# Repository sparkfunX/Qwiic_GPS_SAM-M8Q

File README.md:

SparkFun Ublox GPS Breakout - SAM-M8Q
===========================================================

[*SparkFun Ublox GPS Breakout - SAM-M8Q (SPX-15106)*](https://www.sparkfun.com/products/15106)

The SAM-M8Q is a small GNSS receiver from Ublox with an impressive number of configurations and the ability to communicate over I2C. 

Repository Contents
-------------------

* **/Documents** - Ublox datasheets and various whitepapers around RTK
* **/Hardware** - Eagle files

Documentation
--------------

* **[Installing an Arduino Library Guide](https://learn.sparkfun.com/tutorials/installing-an-arduino-library)** - Basic information on how to install an Arduino library.
* **[Arduino Library](https://github.com/sparkfun/SparkFun_Ublox_Arduino_Library)** - Arduino Library for the SparkFun Ublox GPS-RTK.

License Information
-------------------

This product is _**open source**_! 

Various bits of the code have different licenses applied. Anything SparkFun wrote is beerware; if you see me (or any other SparkFun employee) at the local, and you've found our code helpful, please buy us a round!

Please use, reuse, and modify these files as you see fit. Please maintain attribution to SparkFun Electronics and release anything derivative under the same license.

Distributed as-is; no warranty is given.

- Your friends at SparkFun.

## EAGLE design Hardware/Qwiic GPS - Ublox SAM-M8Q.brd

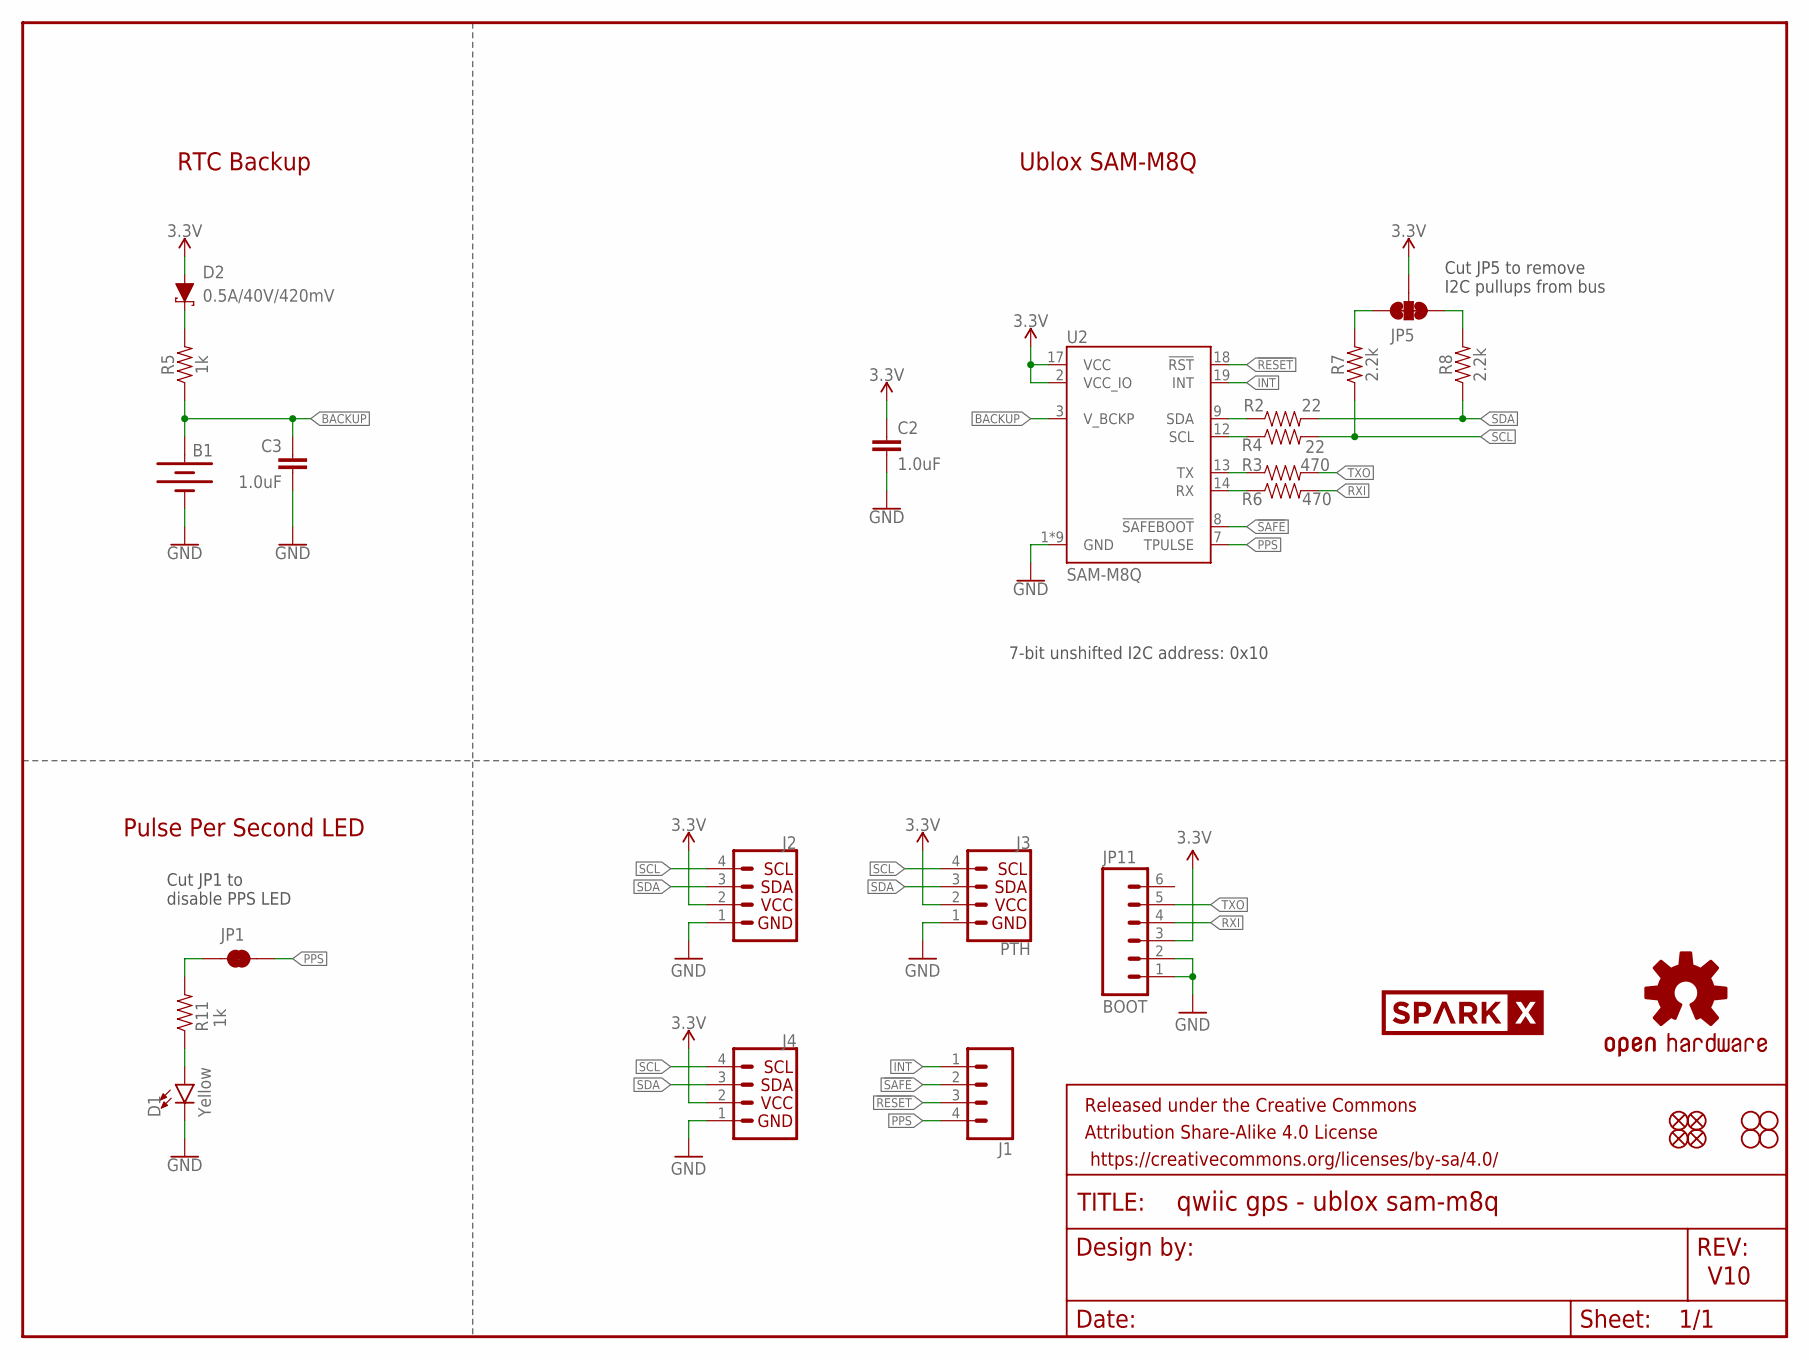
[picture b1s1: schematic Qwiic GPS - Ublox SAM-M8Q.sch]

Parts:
B1: 6.8MM_COIN_CELL; ML414H_IV01E
C2, C3: 1.0uF; 0603
D1: Yellow; LED-0603
D2: 0.5A/40V/420mV; SOD-323
FRAME1: FRAME-LETTER; CREATIVE_COMMONS
J1: CONN_041X04_NO_SILK; 1X04_NO_SILK
J2, J4: I2C_STANDARDQWIIC; 1X04_1MM_RA
J3: PTH; 1X04_NO_SILK
JP1: JUMPER-SMT_2_NC_TRACE_SILK; SMT-JUMPER_2_NC_TRACE_SILK
JP2, JP6, JP7, JP8: FIDUCIALUFIDUCIAL; MICRO-FIDUCIAL
JP3, JP4, JP9, JP10: STAND-OFF
JP5: JUMPER-SMT_3_2-NC_TRACE_SILK; SMT-JUMPER_3_2-NC_TRACE_SILK
JP11: BOOT; 1X06_NO_SILK
LOGO1: OSHW-LOGOMINI; OSHW-LOGO-MINI
R2, R4: 22; 0603
R3, R6: 470; 0603
R5, R11: 1k; 0603
R7, R8: 2.2k; 0603
U2: SAM-M8Q
U$31: SPARKX-LOGO4; SPARKX-MEDIUM

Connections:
3.3V: C2.1, D2.A, J2.2, J3.2 (VCC), J4.2, JP5.2, JP11.3, U2.2 (VCC_IO), U2.17 (VCC)
!RESET: J1.3, U2.18 (!RST)
!SAFE: J1.2, U2.8 (!SAFEBOOT)
BACKUP: B1.+, C3.1, R5.1, U2.3 (V_BCKP)
GND: B1.-, C2.2, C3.2, D1.C, J2.1, J3.1 (GND), J4.1, JP11.1, JP11.2, U2.1 (GND), U2.4 (GND), U2.5 (GND), U2.6 (GND), U2.10 (GND), U2.11 (GND), U2.15 (GND), U2.16 (GND), U2.20 (GND)
INT: J1.1, U2.19 (INT)
unnamed: D1.A, R11.1
unnamed: JP1.1, R11.2
unnamed: JP5.1, R8.2
unnamed: D2.C, R5.2
unnamed: JP5.3, R7.2
PPS: J1.4, JP1.2, U2.7 (TPULSE)
RXI: JP11.4, R6.2
RXLV: R6.1, U2.14 (RX)
SCL: J2.4, J3.4 (SCL), J4.4, R4.2, R7.1
SCL_LV: R4.1, U2.12 (SCL)
SDA: J2.3, J3.3 (SDA), J4.3, R2.2, R8.1
SDA_LV: R2.1, U2.9 (SDA)
TXLV: R3.1, U2.13 (TX)
TXO: JP11.5, R3.2

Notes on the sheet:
V10
7-bit unshifted I2C address: 0x10
Ublox SAM-M8Q
RTC Backup
Pulse Per Second LED
Cut JP5 to remove I2C pullups from bus
Cut JP1 to disable PPS LED

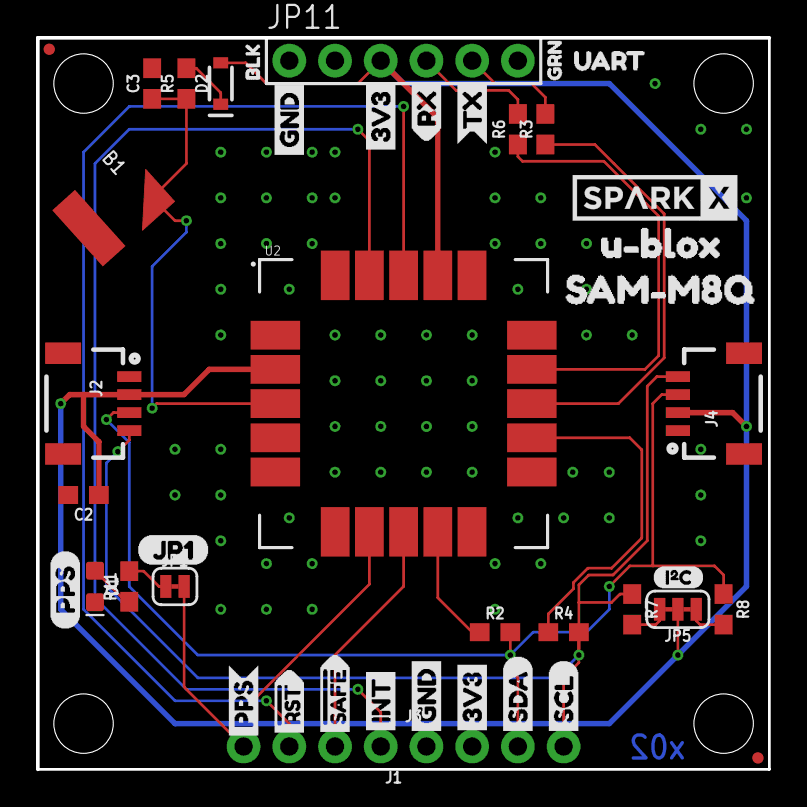
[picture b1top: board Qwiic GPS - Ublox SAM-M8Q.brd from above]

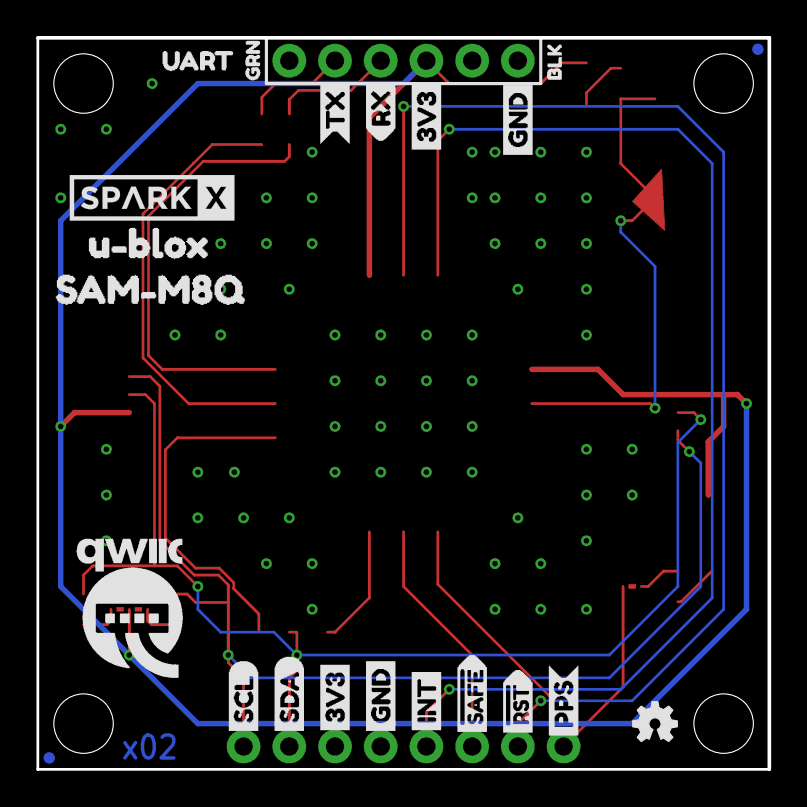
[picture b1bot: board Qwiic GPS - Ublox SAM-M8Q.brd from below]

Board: 2 copper layers, 40.6 x 40.6 mm, 71 parts (22 on the bottom side), 20 nets.

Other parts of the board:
U$1, U$4: SDA-[)
U$2: SPARKX-LOGO4; SPARKX-MEDIUM
U$3, U$5: SCL-[)
U$6, U$7, U$27, U$32: 3V3-04
U$8, U$9, U$33, U$34: GND-04
U$10: I_SUPER2_C-()-03
U$11, U$45: UART0
U$12, U$13: BLK1
U$14, U$17: GRN2
U$15, U$16: INT8
U$18: JP10
U$19, U$20: RX6
U$21, U$25: SAM#M8Q4
U$22, U$26: U#BLOX3
U$23, U$24: TX7
U$28: QWIIC-LOGO-LARGE
U$29: PPS0
U$35, U$36: #RST3
U$39, U$40: #SAFE1
U$43, U$44: PPS5

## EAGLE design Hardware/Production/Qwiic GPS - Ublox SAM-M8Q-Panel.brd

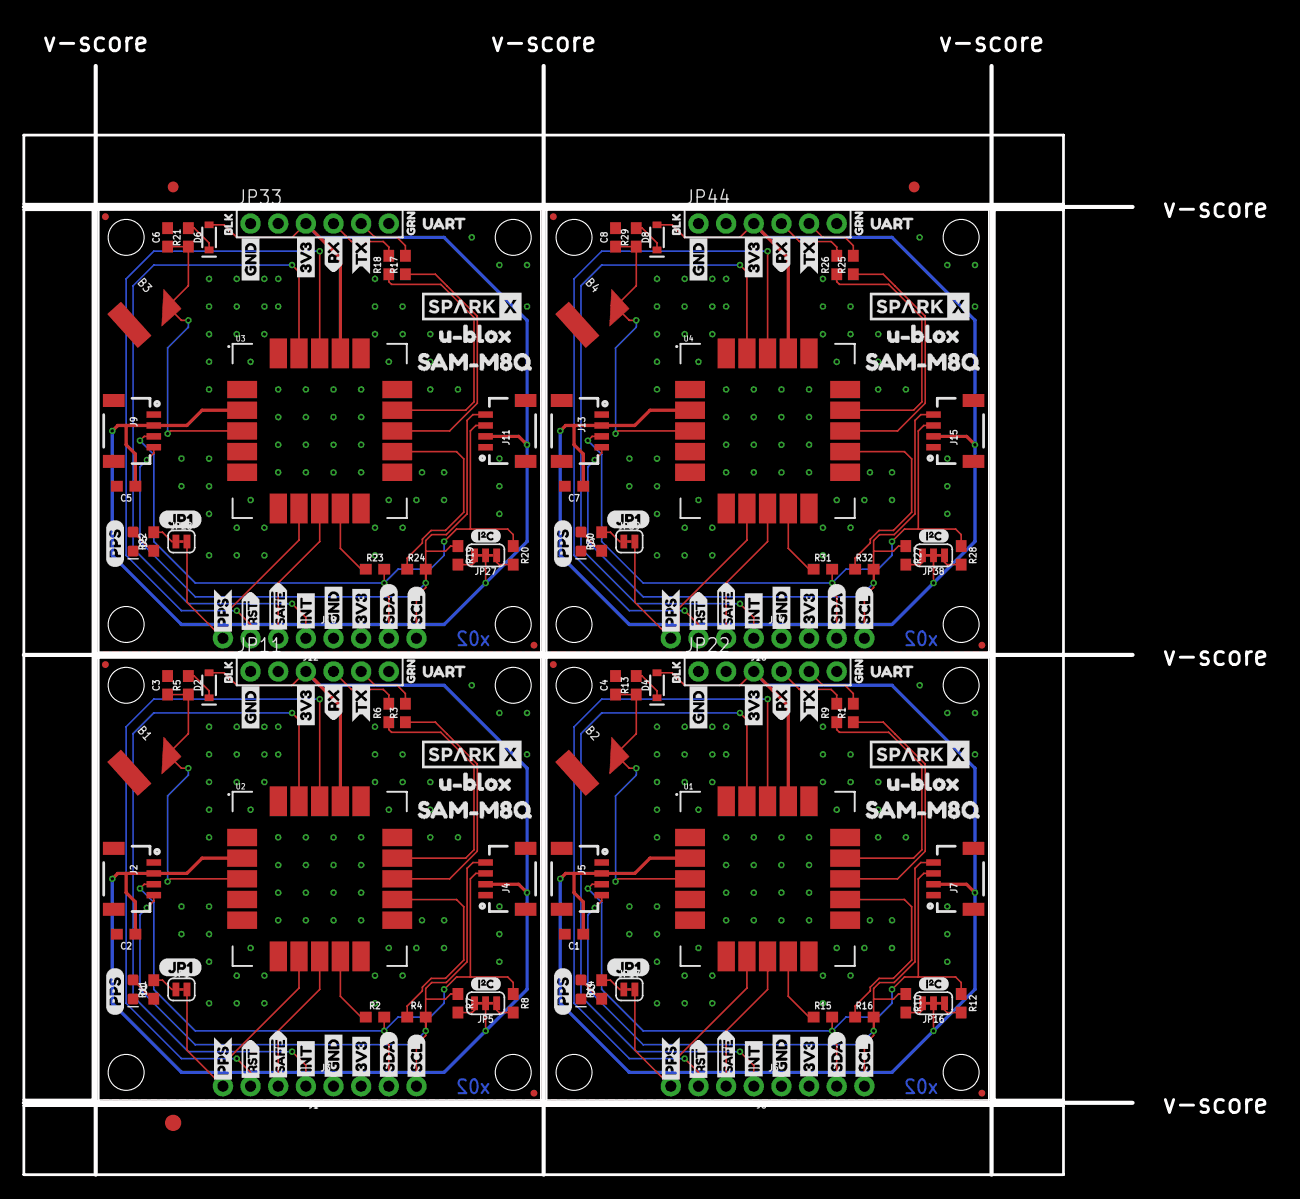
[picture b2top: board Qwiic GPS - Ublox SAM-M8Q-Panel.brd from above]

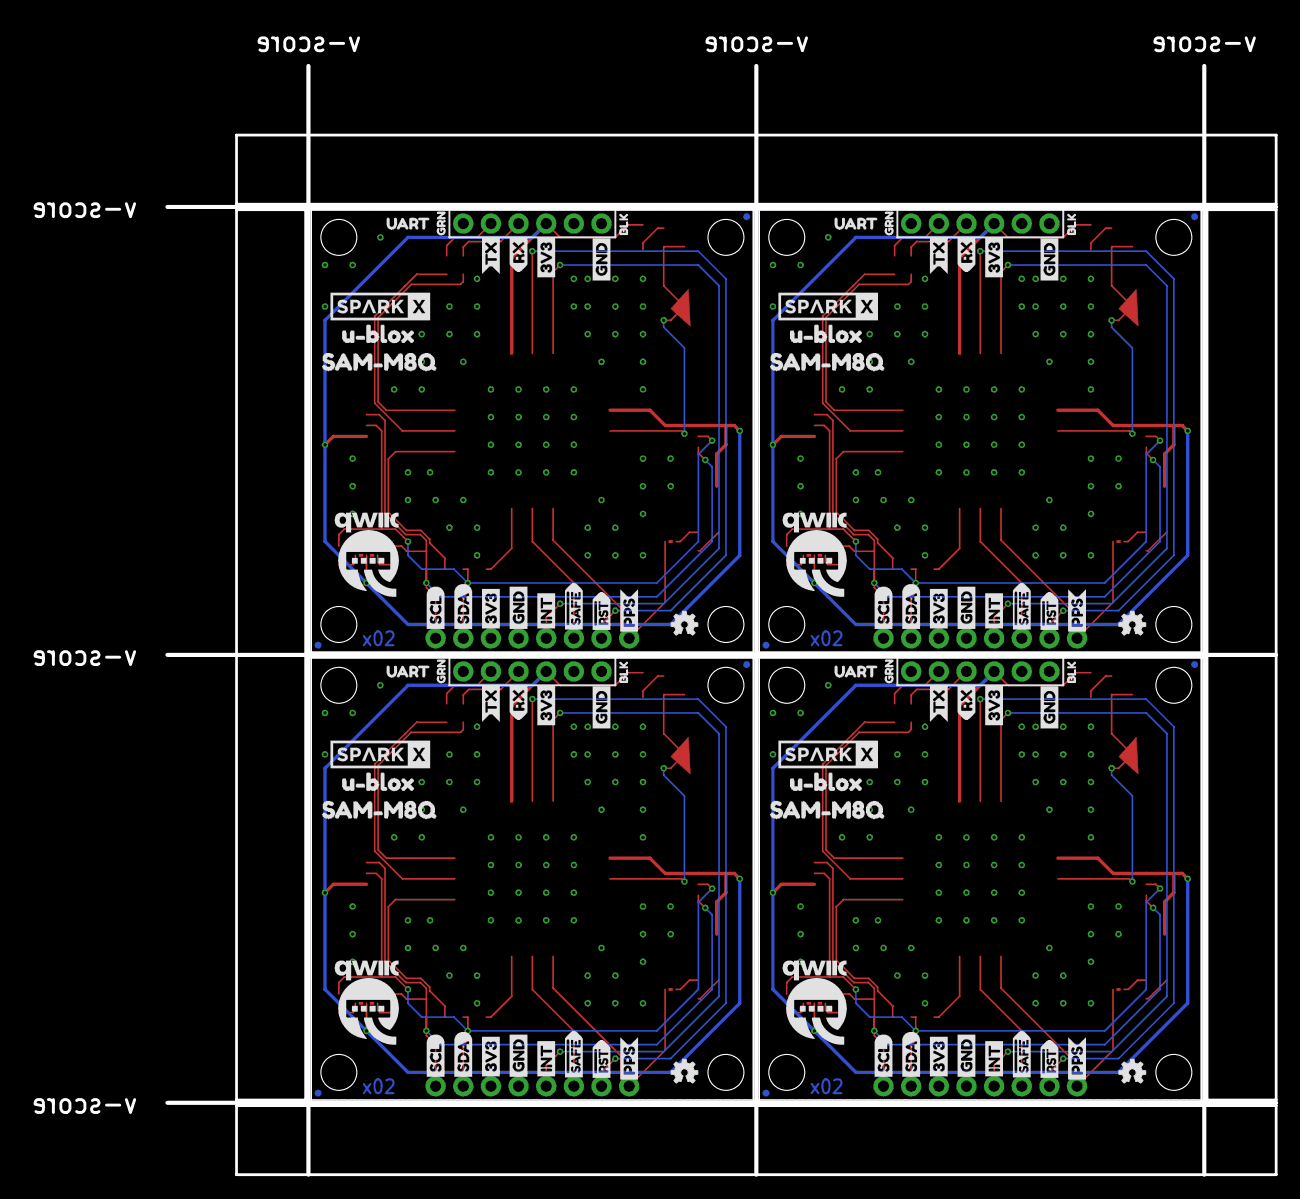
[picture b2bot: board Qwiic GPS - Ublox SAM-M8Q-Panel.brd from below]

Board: 2 copper layers, 101.9 x 101.9 mm, 283 parts (88 on the bottom side), 80 nets.

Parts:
B1, B2, B3, B4: 6.8MM_COIN_CELL; ML414H_IV01E
C1, C2, C3, C4, C5, C6, C7, C8: 1.0uF; 0603
D1, D3, D5, D7: Yellow; LED-0603
D2, D4, D6, D8: 0.5A/40V/420mV; SOD-323
E$1, E$2: FIDUCIAL-1X2
E$3: FIDUCIAL-1.5X3
J1, J8, J12, J16: 1X04_NO_SILK
J2, J4, J5, J7, J9, J11, J13, J15: 1X04_1MM_RA
J3, J6, J10, J14: PTH; 1X04_NO_SILK
JP1, JP17, JP28, JP39: SMT-JUMPER_2_NC_TRACE_SILK
JP2, JP6, JP7, JP8, JP14, JP15, JP18, JP19, JP25, JP26, JP29, JP30, JP36, JP37, JP40, JP41: FIDUCIALUFIDUCIAL; MICRO-FIDUCIAL
JP3, JP4, JP9, JP10, JP12, JP13, JP20, JP21, JP23, JP24, JP31, JP32, JP34, JP35, JP42, JP43: STAND-OFF
JP5, JP16, JP27, JP38: SMT-JUMPER_3_2-NC_TRACE_SILK
JP11, JP22, JP33, JP44: BOOT; 1X06_NO_SILK
LOGO1, LOGO2, LOGO3, LOGO4: OSHW-LOGOMINI; OSHW-LOGO-MINI
R1, R3, R6, R9, R17, R18, R25, R26: 470; 0603
R2, R4, R15, R16, R23, R24, R31, R32: 22; 0603
R5, R11, R13, R14, R21, R22, R29, R30: 1k; 0603
R7, R8, R10, R12, R19, R20, R27, R28: 2.2k; 0603
U1, U2, U3, U4: SAM-M8Q
U$1, U$4, U$30, U$38, U$81, U$83, U$121, U$123: SDA-[)
U$2, U$31, U$61, U$62, U$101, U$102, U$141, U$142: SPARKX-LOGO4; SPARKX-MEDIUM
U$3, U$5, U$37, U$41, U$82, U$84, U$122, U$124: SCL-[)
U$6, U$7, U$27, U$32, U$42, U$46, U$63, U$64, U$85, U$86, U$103, U$104, U$125, U$126, U$143, U$144: 3V3-04
U$8, U$9, U$33, U$34, U$47, U$48, U$65, U$66, U$87, U$88, U$105, U$106, U$127, U$128, U$145, U$146: GND-04
U$10, U$49, U$89, U$129: I_SUPER2_C-()-03
U$11, U$45, U$73, U$74, U$113, U$114, U$153, U$154: UART0
U$12, U$13, U$75, U$76, U$115, U$116, U$155, U$156: BLK1
U$14, U$17, U$77, U$78, U$117, U$118, U$157, U$158: GRN2
U$15, U$16, U$50, U$51, U$90, U$91, U$130, U$131: INT8
U$18, U$79, U$119, U$159: JP10
U$19, U$20, U$52, U$53, U$92, U$93, U$132, U$133: RX6
U$21, U$25, U$54, U$59, U$94, U$99, U$134, U$139: SAM#M8Q4
U$22, U$26, U$57, U$58, U$97, U$98, U$137, U$138: U#BLOX3
U$23, U$24, U$55, U$56, U$95, U$96, U$135, U$136: TX7
U$28, U$80, U$120, U$160: QWIIC-LOGO-LARGE
U$29, U$60, U$100, U$140: PPS0
U$35, U$36, U$67, U$68, U$107, U$108, U$147, U$148: #RST3
U$39, U$40, U$69, U$70, U$109, U$110, U$149, U$150: #SAFE1
U$43, U$44, U$71, U$72, U$111, U$112, U$151, U$152: PPS5

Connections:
3.3V: C2.1, D2.A, J2.2, J3.2, J4.2, JP5.2, JP11.3, U2.2, U2.17
3.3V1: C1.1, D4.A, J5.2, J6.2, J7.2, JP16.2, JP22.3, U1.2, U1.17
3.3V2: C5.1, D6.A, J9.2, J10.2, J11.2, JP27.2, JP33.3, U3.2, U3.17
3.3V3: C7.1, D8.A, J13.2, J14.2, J15.2, JP38.2, JP44.3, U4.2, U4.17
!RESET: J1.3, U2.18
!RESET1: J8.3, U1.18
!RESET2: J12.3, U3.18
!RESET3: J16.3, U4.18
!SAFE: J1.2, U2.8
!SAFE1: J8.2, U1.8
!SAFE2: J12.2, U3.8
!SAFE3: J16.2, U4.8
BACKUP: B1.+, C3.1, R5.1, U2.3
BACKUP1: B2.+, C4.1, R13.1, U1.3
BACKUP2: B3.+, C6.1, R21.1, U3.3
BACKUP3: B4.+, C8.1, R29.1, U4.3
GND: B1.-, C2.2, C3.2, D1.C, J2.1, J3.1, J4.1, JP11.1, JP11.2, U2.1, U2.4, U2.5, U2.6, U2.10, U2.11, U2.15, U2.16, U2.20
GND1: B2.-, C1.2, C4.2, D3.C, J5.1, J6.1, J7.1, JP22.1, JP22.2, U1.1, U1.4, U1.5, U1.6, U1.10, U1.11, U1.15, U1.16, U1.20
GND2: B3.-, C5.2, C6.2, D5.C, J9.1, J10.1, J11.1, JP33.1, JP33.2, U3.1, U3.4, U3.5, U3.6, U3.10, U3.11, U3.15, U3.16, U3.20
GND3: B4.-, C7.2, C8.2, D7.C, J13.1, J14.1, J15.1, JP44.1, JP44.2, U4.1, U4.4, U4.5, U4.6, U4.10, U4.11, U4.15, U4.16, U4.20
INT: J1.1, U2.19
INT1: J8.1, U1.19
INT2: J12.1, U3.19
INT3: J16.1, U4.19
unnamed: JP16.1, R12.2
unnamed: D1.A, R11.1
unnamed: JP16.3, R10.2
unnamed: JP1.1, R11.2
unnamed: JP5.1, R8.2
unnamed: D2.C, R5.2
unnamed: D3.A, R14.1
unnamed: JP5.3, R7.2
unnamed: JP17.1, R14.2
unnamed: D4.C, R13.2
unnamed: JP27.1, R20.2
unnamed: JP27.3, R19.2
unnamed: D5.A, R22.1
unnamed: JP28.1, R22.2
unnamed: D6.C, R21.2
unnamed: JP38.1, R28.2
unnamed: JP38.3, R27.2
unnamed: D7.A, R30.1
unnamed: JP39.1, R30.2
unnamed: D8.C, R29.2
PPS: J1.4, JP1.2, U2.7
PPS1: J8.4, JP17.2, U1.7
PPS2: J12.4, JP28.2, U3.7
PPS3: J16.4, JP39.2, U4.7
RXI: JP11.4, R6.2
RXI1: JP22.4, R9.2
RXI2: JP33.4, R18.2
RXI3: JP44.4, R26.2
RXLV: R6.1, U2.14
RXLV1: R9.1, U1.14
RXLV2: R18.1, U3.14
RXLV3: R26.1, U4.14
SCL: J2.4, J3.4, J4.4, R4.2, R7.1
SCL1: J5.4, J6.4, J7.4, R10.1, R16.2
SCL2: J9.4, J10.4, J11.4, R19.1, R24.2
SCL3: J13.4, J14.4, J15.4, R27.1, R32.2
SCL_LV: R4.1, U2.12
SCL_LV1: R16.1, U1.12
SCL_LV2: R24.1, U3.12
SCL_LV3: R32.1, U4.12
SDA: J2.3, J3.3, J4.3, R2.2, R8.1
SDA1: J5.3, J6.3, J7.3, R12.1, R15.2
SDA2: J9.3, J10.3, J11.3, R20.1, R23.2
SDA3: J13.3, J14.3, J15.3, R28.1, R31.2
SDA_LV: R2.1, U2.9
SDA_LV1: R15.1, U1.9
SDA_LV2: R23.1, U3.9
SDA_LV3: R31.1, U4.9
TXLV: R3.1, U2.13
TXLV1: R1.1, U1.13
TXLV2: R17.1, U3.13
TXLV3: R25.1, U4.13
TXO: JP11.5, R3.2
TXO1: JP22.5, R1.2
TXO2: JP33.5, R17.2
TXO3: JP44.5, R25.2

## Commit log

2018-11-27 Removing single unit files. Removing notes from schematic.
2018-11-27 Adding readme
2019-03-12 Updated battery footprint
    Footprint for the battery is now for the reflowable version

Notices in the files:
parts and their libraries:
SparkFun-Resistors: Licensing: Creative Commons ShareAlike 4.0 International - https://creativecommons.org/licenses/by-sa/4.0
SparkFun-Aesthetics: Released under the Creative Commons Attribution Share-Alike 4.0 License
SparkFun-Aesthetics: https://creativecommons.org/licenses/by-sa/4.0
